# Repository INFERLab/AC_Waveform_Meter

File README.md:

# AC Waveform Meter 
Arduino-based Open-source AC Waveform meter in a shield form factor for the Raspberry Pi 3. This low-cost AC power meter is designed to continuously measure voltage and current waveforms at up to 14 kHz.

## Repository Contents
- **/hardware** - All Eagle designs files (.brd, .sch)
- **/src** - Source files for the power meter and Raspberry Pi 3
- **/extras** - Additional documentation for the power meter
- **/examples** - Example sketches for the power meter in .ino (run these from the Arduino IDE) and .c

## Wiki
Set up details for the micro controller firmware and the Raspberry Pi 3.

## Version History
- V1.0 - Initial Release

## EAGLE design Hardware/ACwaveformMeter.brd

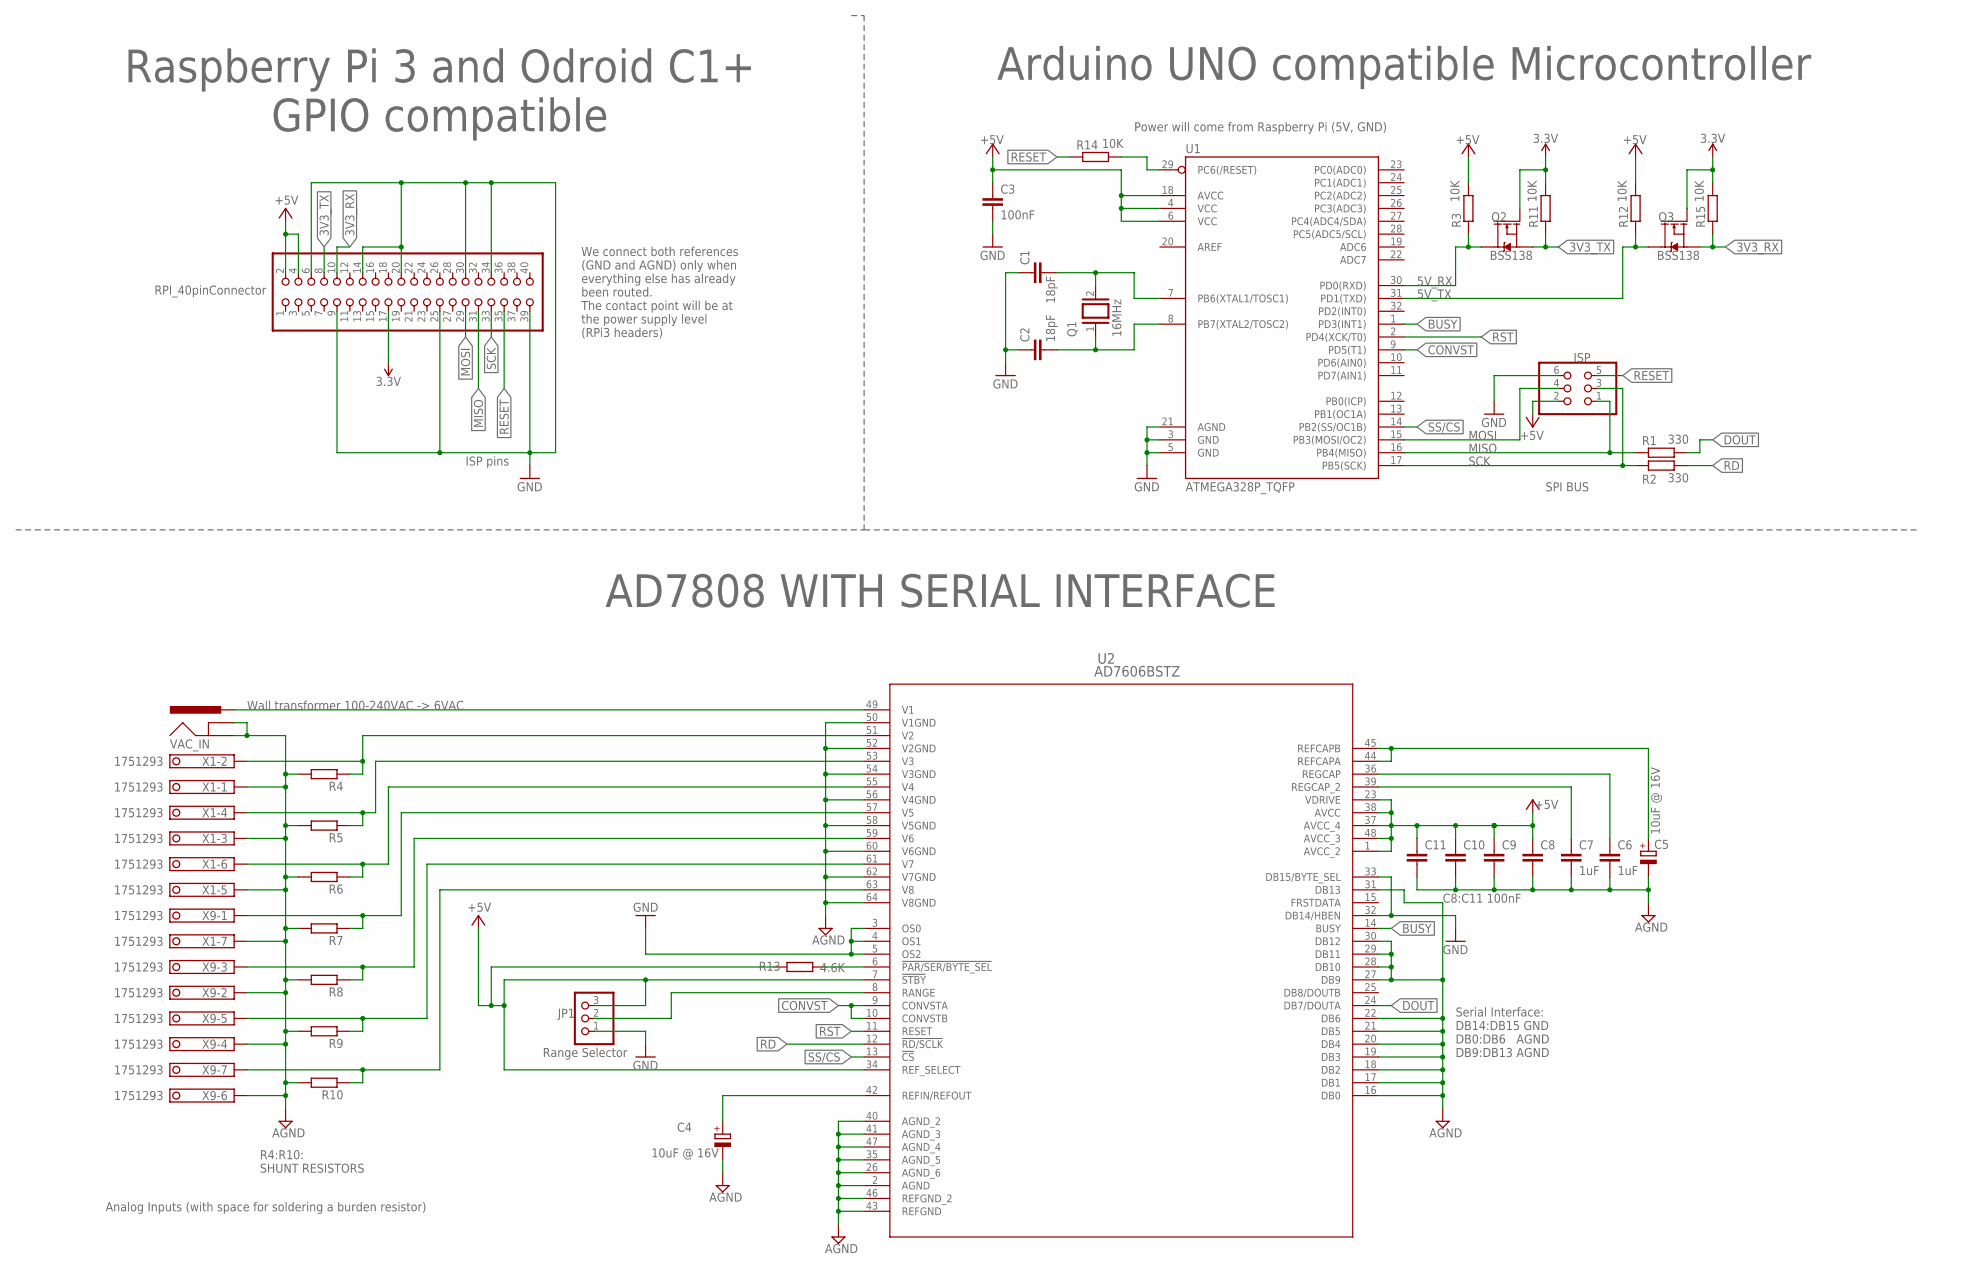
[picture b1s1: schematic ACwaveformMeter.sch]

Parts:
C1, C2: 18pF; C0402
C3, C8, C9, C10, C11: 100nF; C0402
C4, C5: 10uF @ 16V; 153CLV-0405
C6, C7: 1uF; C0402
ISP: ISP6pin; 2X03
JP1: PINHD-1X3; 1X03
Q1: 16MHz; QS
Q2, Q3: BSS138; SOT23-3
R1, R2: 330; R0402
R3, R11, R12, R14, R15: 10K; R0402
R4, R5, R6, R7, R8, R9, R10: R-EU_M1206; M1206
R13: 4.6K; R0402
RASPBERRY_PI3: RPI_40pinConnector; 2X20
U1: ATMEGA328P_TQFP; TQFP32-08
U2: AD7606BSTZ; ST_64_2
VAC_IN: POWER_JACKPTH_LOCK; POWER_JACK_PTH_LOCK
X1, X9: 1751293

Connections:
3.3V: Q2.1 (G), Q3.1 (G), R11.2, R15.2, RASPBERRY_PI3.17
3V3_RX: Q3.2 (S), R15.1, RASPBERRY_PI3.10
3V3_TX: Q2.2 (S), R11.1, RASPBERRY_PI3.8
5V_RX: Q2.3 (D), R3.1, U1.30 (PD0(RXD))
5V_TX: Q3.3 (D), R12.1, U1.31 (PD1(TXD))
+5V: C3.1, C8.1, C9.1, C10.1, C11.1, ISP.2, JP1.3, R3.2, R12.2, R13.1, RASPBERRY_PI3.2, RASPBERRY_PI3.4, U1.4 (VCC), U1.6 (VCC), U1.18 (AVCC), U2.1 (AVCC_2), U2.7 (!STBY), U2.23 (VDRIVE), U2.34 (REF_SELECT), U2.37 (AVCC_4), U2.38 (AVCC), U2.48 (AVCC_3)
BUSY: U1.1 (PD3(INT1)), U2.14 (BUSY)
CONVST: U1.9 (PD5(T1)), U2.9 (CONVSTA), U2.10 (CONVSTB)
DOUT: R1.2, U2.24 (DB7/DOUTA)
GND: C1.1, C2.1, C3.2, C4.-, C5.-, C6.2, C7.2, C8.2, C9.2, C10.2, C11.2, ISP.6, JP1.1, R4.2, R5.2, R6.2, R7.2, R8.2, R9.2, R10.2, RASPBERRY_PI3.6, RASPBERRY_PI3.9, RASPBERRY_PI3.14, RASPBERRY_PI3.20, RASPBERRY_PI3.25, RASPBERRY_PI3.30, RASPBERRY_PI3.34, RASPBERRY_PI3.39, U1.3 (GND), U1.5 (GND), U1.21 (AGND), U2.2 (AGND), U2.3 (OS0), U2.4 (OS1), U2.5 (OS2), U2.16 (DB0), U2.17 (DB1), U2.18 (DB2), U2.19 (DB3), U2.20 (DB4), U2.21 (DB5), U2.22 (DB6), U2.26 (AGND_6), U2.27 (DB9), U2.28 (DB10), U2.29 (DB11), U2.30 (DB12), U2.31 (DB13), U2.32 (DB14/HBEN), U2.33 (DB15/BYTE_SEL), U2.35 (AGND_5), U2.40 (AGND_2), U2.41 (AGND_3), U2.43 (REFGND), U2.46 (REFGND_2), U2.47 (AGND_4), U2.50 (V1GND), U2.52 (V2GND), U2.54 (V3GND), U2.56 (V4GND), U2.58 (V5GND), U2.60 (V6GND), U2.62 (V7GND), U2.64 (V8GND), VAC_IN.GND, VAC_IN.GNDBREAK, X1.1, X1.3, X1.5, X1.7, X9.2, X9.4, X9.6
MISO: ISP.1, R1.1, RASPBERRY_PI3.31, U1.16 (PB4(MISO))
MOSI: ISP.4, RASPBERRY_PI3.29, U1.15 (PB3(MOSI/OC2))
unnamed: C5.+, U2.44 (REFCAPA), U2.45 (REFCAPB)
unnamed: C4.+, U2.42 (REFIN/REFOUT)
unnamed: U2.49 (V1), VAC_IN.PWR
unnamed: C6.1, U2.36 (REGCAP)
unnamed: C7.1, U2.39 (REGCAP_2)
unnamed: C1.2, Q1.2, U1.7 (PB6(XTAL1/TOSC1))
unnamed: C2.2, Q1.1, U1.8 (PB7(XTAL2/TOSC2))
unnamed: R14.2, U1.29 (PC6(/RESET))
unnamed: JP1.2, U2.8 (RANGE)
unnamed: R13.2, U2.6 (!PAR/SER/BYTE_SEL)
unnamed: R4.1, U2.51 (V2), X1.2
unnamed: R5.1, U2.53 (V3), X1.4
unnamed: R6.1, U2.55 (V4), X1.6
unnamed: R7.1, U2.57 (V5), X9.1
unnamed: R8.1, U2.59 (V6), X9.3
unnamed: R9.1, U2.61 (V7), X9.5
unnamed: R10.1, U2.63 (V8), X9.7
RD: R2.2, U2.12 (!RD/SCLK)
RESET: ISP.5, R14.1, RASPBERRY_PI3.35
RST: U1.2 (PD4(XCK/T0)), U2.11 (RESET)
SCK: ISP.3, R2.1, RASPBERRY_PI3.33, U1.17 (PB5(SCK))
SS/CS: U1.14 (PB2(SS/OC1B)), U2.13 (!CS)

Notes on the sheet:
Power will come from Raspberry Pi (5V, GND)
SPI BUS
Analog Inputs (with space for soldering a burden resistor)
C8:C11 100nF
Serial Interface: DB14:DB15 GND DB0:DB6 AGND DB9:DB13 AGND
We connect both references (GND and AGND) only when everything else has already been routed. The contact point will be at the power supply level (RPi3 headers)
Wall transformer 100-240VAC -> 6VAC
R4:R10: SHUNT RESISTORS
Raspberry Pi 3 and Odroid C1+ GPIO compatible
Arduino UNO compatible Microcontroller
Range Selector
AD7808 WITH SERIAL INTERFACE
ISP pins

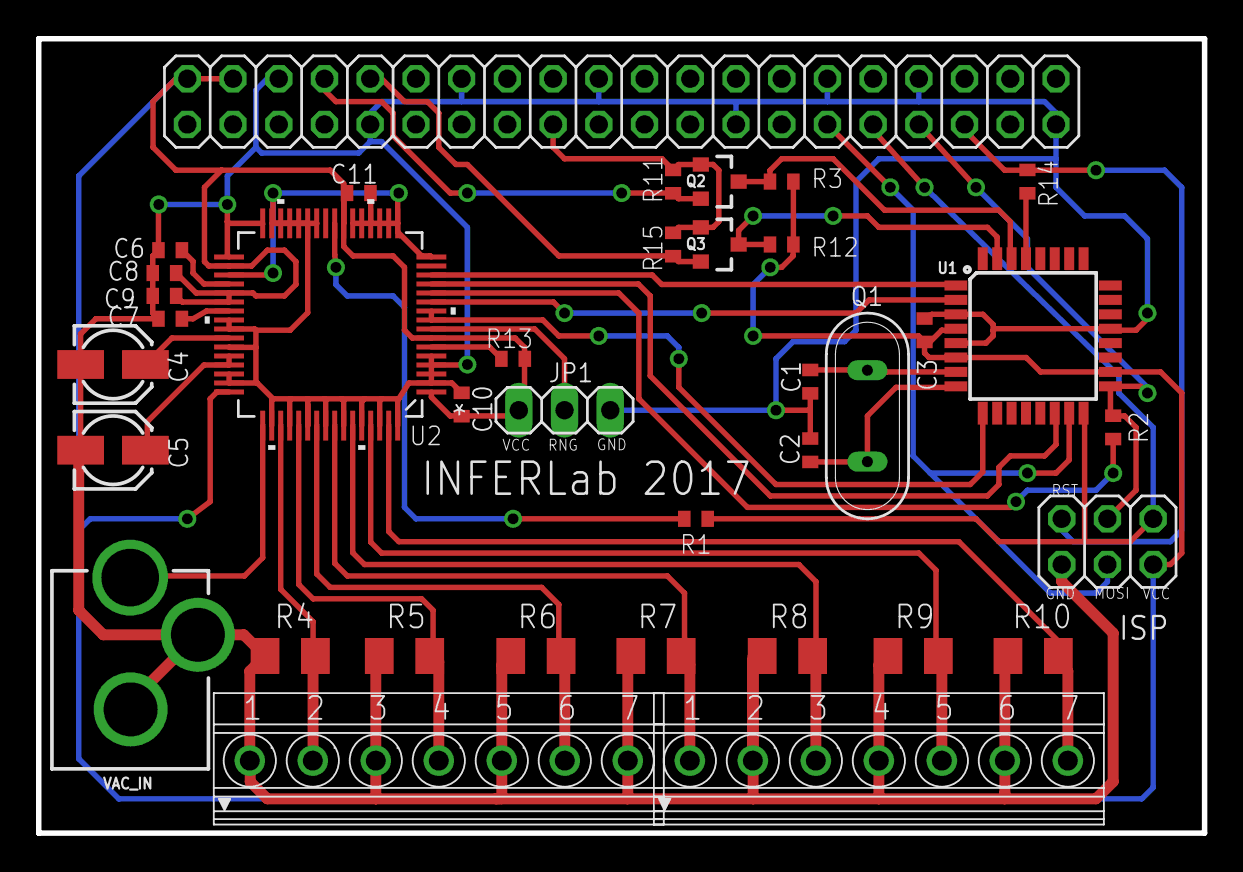
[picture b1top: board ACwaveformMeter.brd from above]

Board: 2 copper layers, 64.8 x 44.1 mm, 37 parts (0 on the bottom side), 34 nets.

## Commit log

2017-09-08 new folders added
2018-03-15 makefile
2018-03-20 skip sample
2018-07-25 Create picture

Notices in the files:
parts and their libraries:
SparkFun-IC-Microcontroller: Licensing: Creative Commons ShareAlike 4.0 International - https://creativecommons.org/licenses/by-sa/4.0
